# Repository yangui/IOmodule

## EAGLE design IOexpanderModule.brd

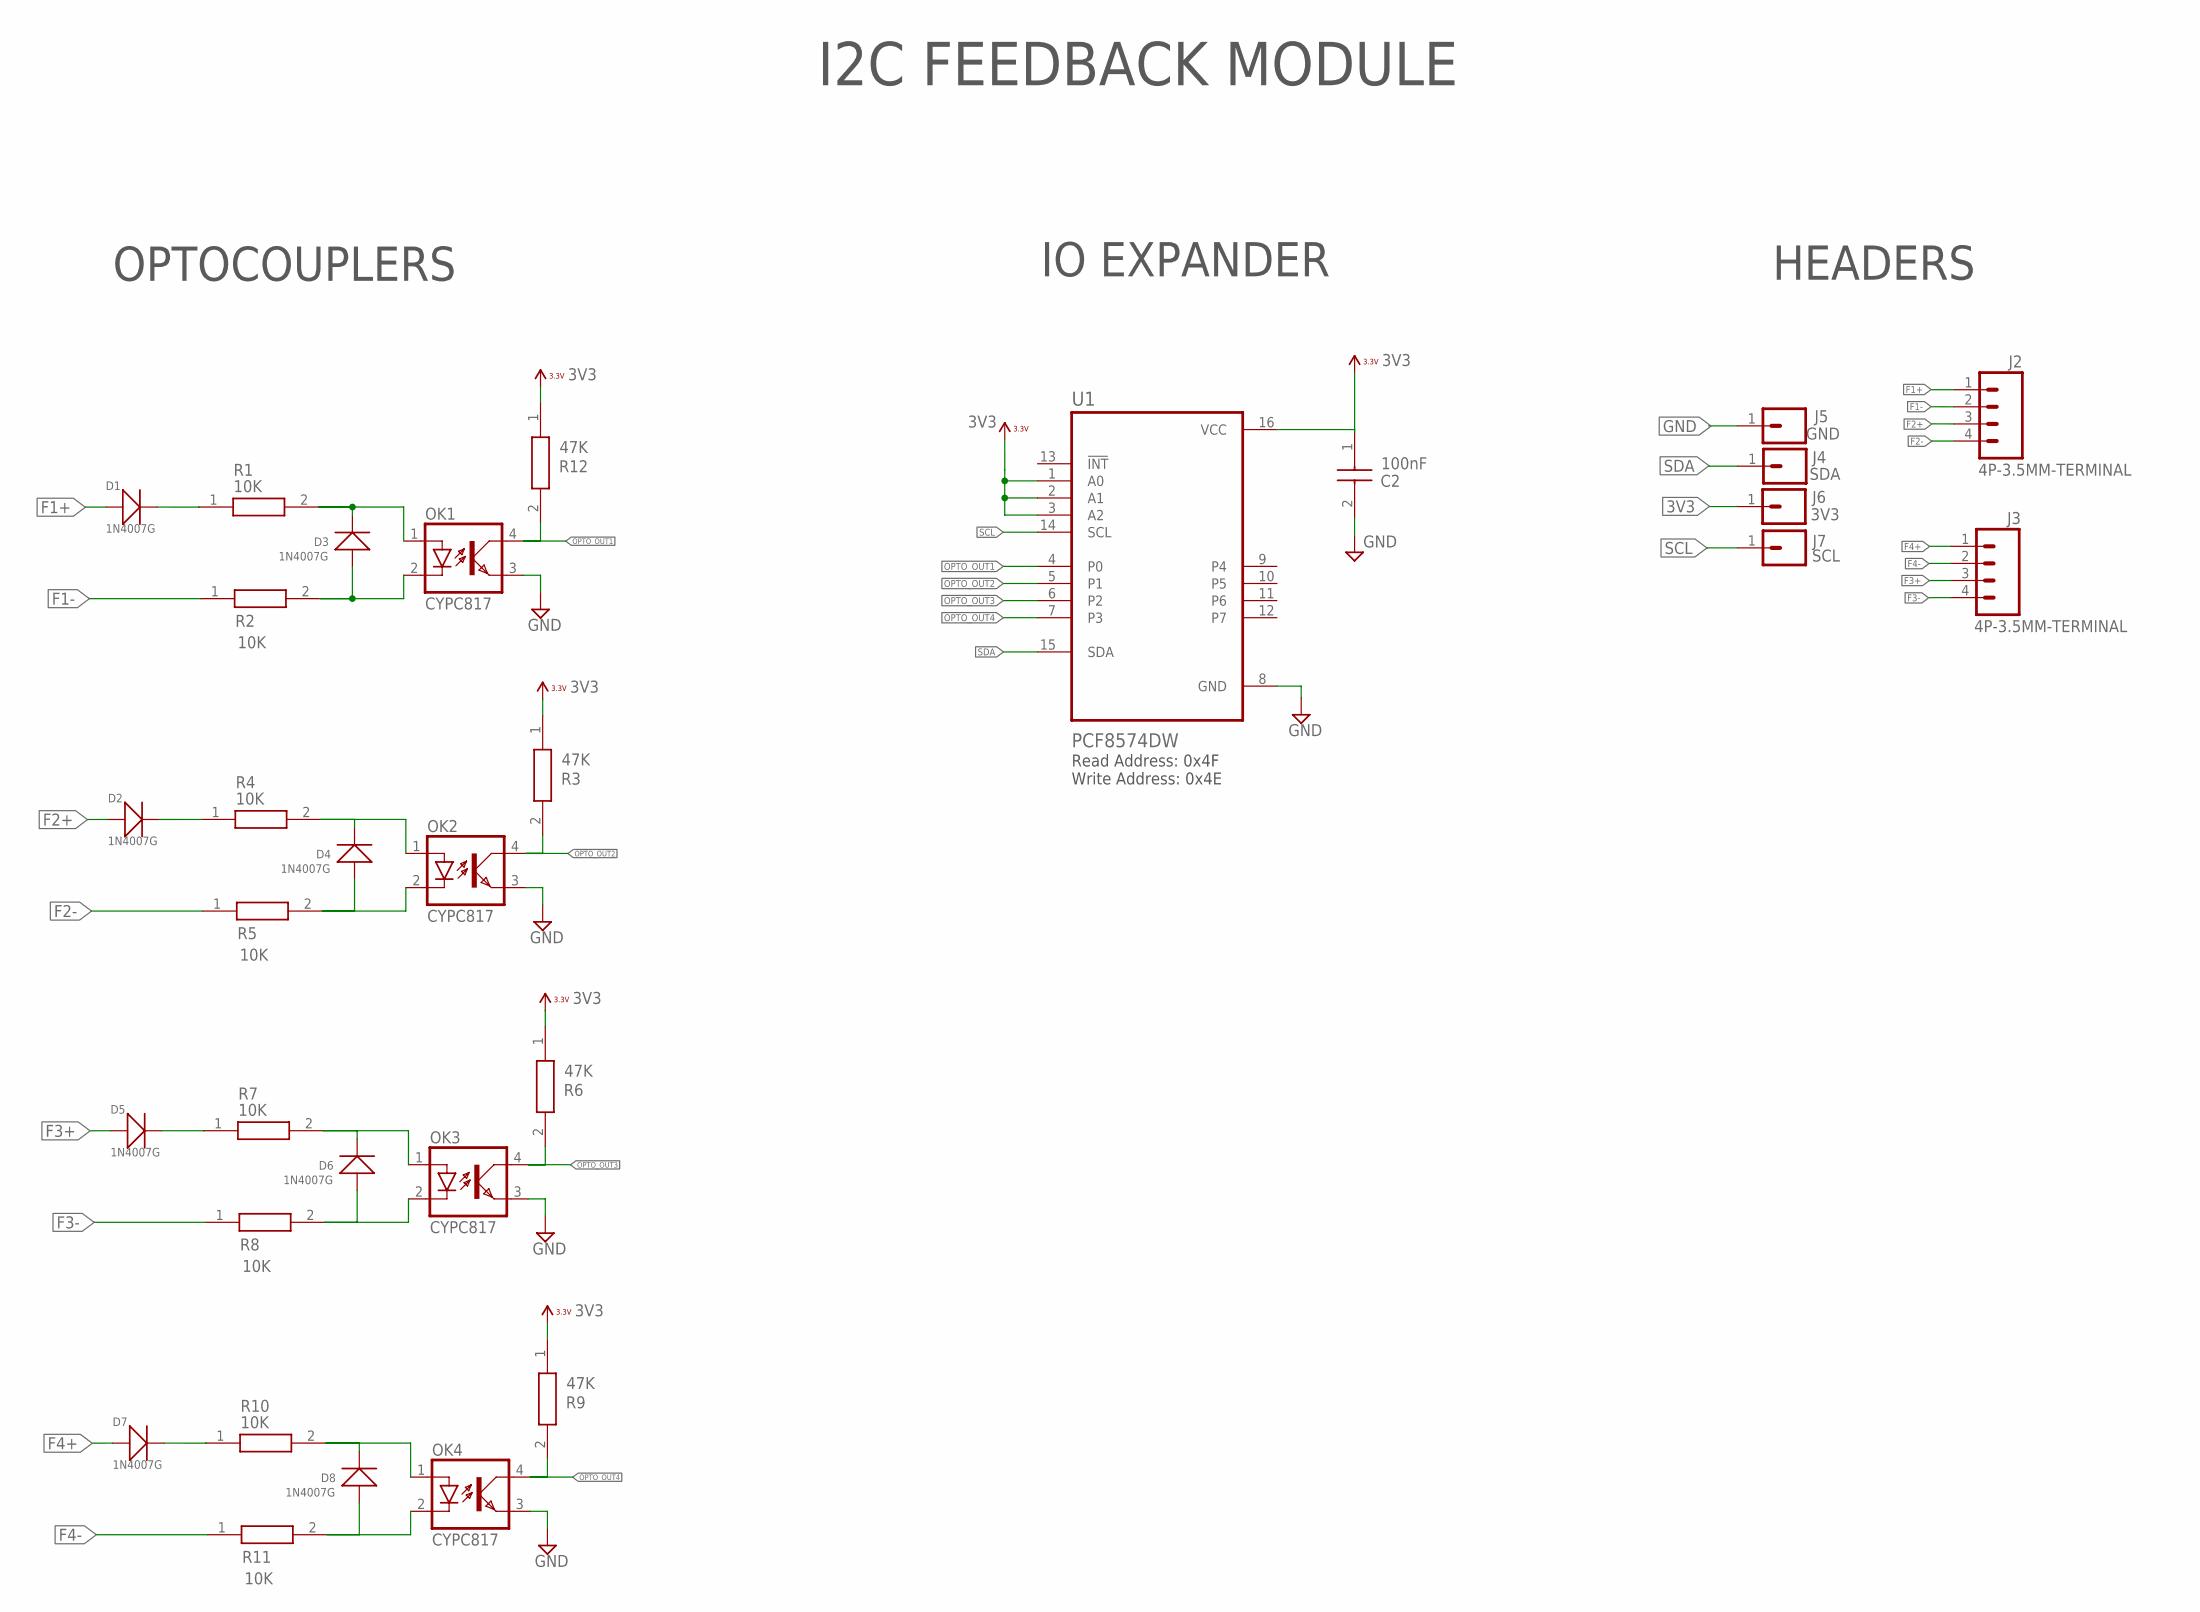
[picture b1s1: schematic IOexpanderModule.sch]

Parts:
C2: 100nF; CAPC1005X55N
D1, D2, D3, D4, D5, D6, D7, D8: 1N4007G; DO-214AC
J2: 4P-3.5MM-TERMINAL; HDRVR4W80P350_1X4_1540X690X920B; PARTNUMBER DB2EVC-3.5-4P-GN
J3: 4P-3.5MM-TERMINAL; HDRVR4W80P350_1X4_1540X690X920B
J4: SDA; 1X01; PARTNUMBER YELLOW 24AWG WIRE 150MM
J5: GND; 1X01; PARTNUMBER BLACK 24AWG WIRE 150MM
J6: 3V3; 1X01; PARTNUMBER RED 24AWG WIRE 150MM
J7: SCL; 1X01; PARTNUMBER GREEN 24AWG WIRE 150MM
OK1, OK2, OK3, OK4: CYPC817; DIL4-SMD
R1, R2, R4, R5, R7, R8, R10, R11: 10K; ERJP06D_1000V
R3, R6, R9, R12: 47K; ERJ2RKD1004X
U1: PCF8574DW; SOIC127P1030X265-16N

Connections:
3V3: C2.1, J6.1, R3.1, R6.1, R9.1, R12.1, U1.1 (A0), U1.2 (A1), U1.3 (A2), U1.16 (VCC)
F1+: D1.1 (+), J2.1
F1-: J2.2, R2.1
F2+: D2.1 (+), J2.3
F2-: J2.4, R5.1
F3+: D5.1 (+), J3.3
F3-: J3.4, R8.1
F4+: D7.1 (+), J3.1
F4-: J3.2, R11.1
GND: C2.2, J5.1, OK1.3 (EMIT), OK2.3 (EMIT), OK3.3 (EMIT), OK4.3 (EMIT), U1.8 (GND)
unnamed: D4.2 (-), OK2.1 (A), R4.2
unnamed: D3.2 (-), OK1.1 (A), R1.2
unnamed: D4.1 (+), OK2.2 (C), R5.2
unnamed: D2.2 (-), R4.1
unnamed: D1.2 (-), R1.1
unnamed: D6.2 (-), OK3.1 (A), R7.2
unnamed: D6.1 (+), OK3.2 (C), R8.2
unnamed: D5.2 (-), R7.1
unnamed: D8.2 (-), OK4.1 (A), R10.2
unnamed: D8.1 (+), OK4.2 (C), R11.2
unnamed: D7.2 (-), R10.1
unnamed: D3.1 (+), OK1.2 (C), R2.2
OPTO_OUT1: OK1.4 (COL), R12.2, U1.4 (P0)
OPTO_OUT2: OK2.4 (COL), R3.2, U1.5 (P1)
OPTO_OUT3: OK3.4 (COL), R6.2, U1.6 (P2)
OPTO_OUT4: OK4.4 (COL), R9.2, U1.7 (P3)
SCL: J7.1, U1.14 (SCL)
SDA: J4.1, U1.15 (SDA)

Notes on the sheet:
IO EXPANDER
HEADERS
OPTOCOUPLERS
Read Address: 0x4F Write Address: 0x4E
I2C FEEDBACK MODULE

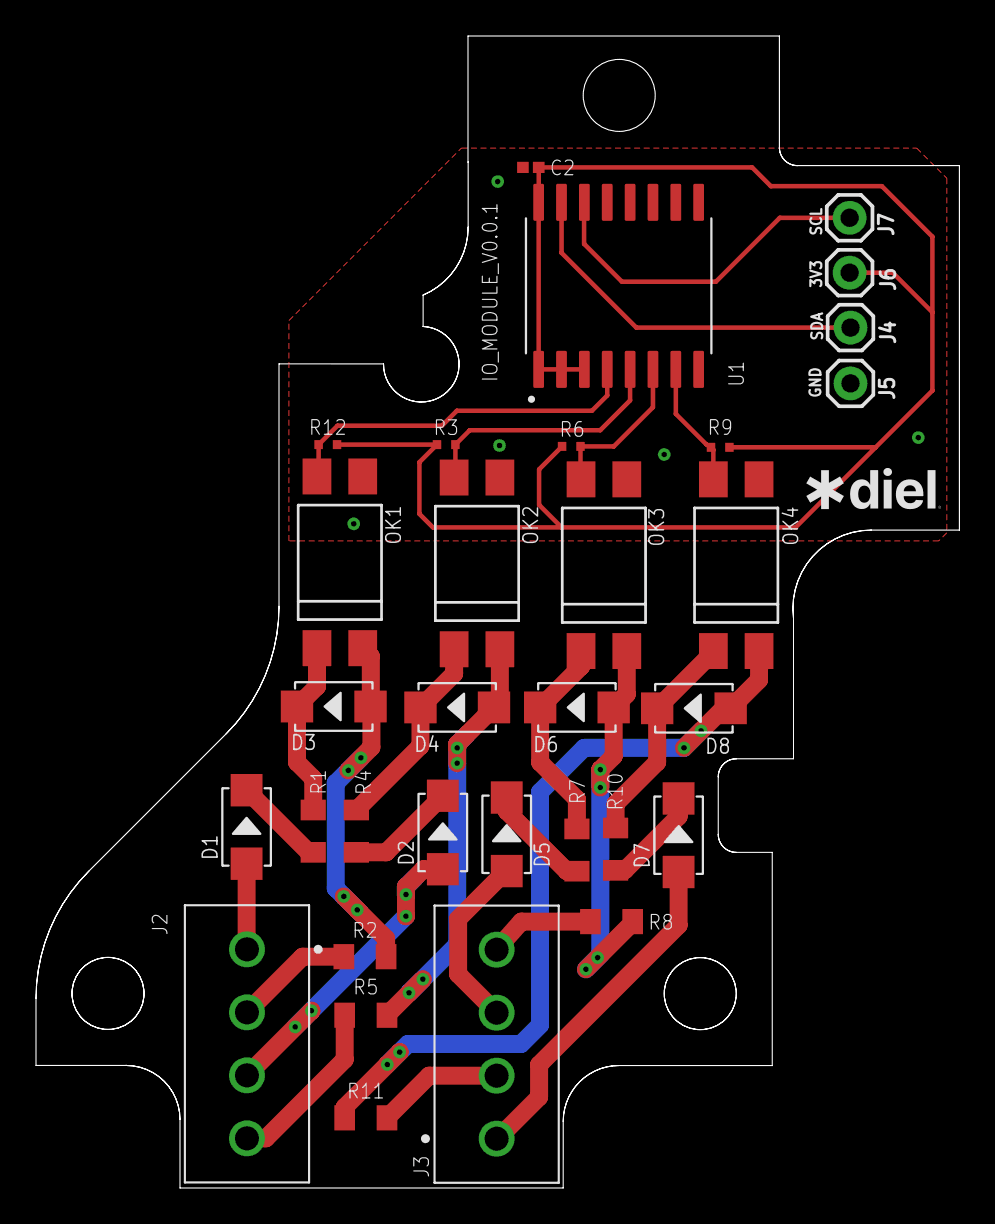
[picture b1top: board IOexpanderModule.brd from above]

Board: 2 copper layers, 51.3 x 64.0 mm, 32 parts (0 on the bottom side), 28 nets.

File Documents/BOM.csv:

"Qty";"Value";"Device";"Package";"Parts";"Description";"PARTNUMBER";"PARTNUMBER2";"PARTNUMBER3";"PARTNUMBER4";
"1";"100nF";"C0402C104K4RAC";"CAPC1005X55N";"C2";"Multilayer Ceramic Capacitors MLCC - SMD/SMT 16volts 0.1uF 10% X7R";"C0402C104K4RAC";"C0402C104K8RAC";"CC0402KRX7R8BB104";"";
"8";"10K";"ERJ-P06J103V";"ERJP06D_1000V";"R1, R2, R4, R5, R7, R8, R10, R11";"Thick Film Resistors - SMD 0805 10Kohms 0.5W 5% AEC-Q200";"ERJ-P06J103V";"SDR10EZPJ103";"ERJ-P06F1002V";"";
"8";"1N4007G";"SMD-DIODE-SCHOTTKY-40V-1A(DO-214AC)";"DO-214AC";"D1, D2, D3, D4, D5, D6, D7, D8";"304020027";"S1M-13-F";"";"";"";
"1";"3V3";"CONN_01_PAD";"1X01";"J6";"";"RED 24AWG WIRE 150MM";"";"";"";
"4";"47K";"ERJ-2RKF4702X";"ERJ2RKD1004X";"R3, R6, R9, R12";"Precision Thick Film Chip Resistor, 47Kohm, 0402, 1/10W";"ERJ-2RKF4702X";"ERJ-2GEJ473X";"RCS040247K0FKED";"";
"2";"4P-3.5MM-TERMINAL";"TERMINAL-PLUG-4P-3,5TERMINAL-3.5-4P";"HDRVR4W80P350_1X4_1540X690X920B";"J2, J3";"TERMINAL BLOCK, 3.5MM PITCH, 4 POLES, 180 DEGREES";"DB2EVC-3.5-4P-GN";"KF2EDGV-3.5-4P";"395016004";"284514-4";
"4";"CYPC817";"LTV816S";"DIL4-SMD";"OK1, OK2, OK3, OK4";"OPTO COUPLER";"CYPC817(C-TP2)";"TPC817S1C RAG";"";"";
"1";"GND";"CONN_01_PAD";"1X01";"J5";"";"BLACK 24AWG WIRE 150MM";"";"";"";
"1";"PCF8574DW";"PCF8574DW";"SOIC127P1030X265-16N";"U1";"8-bit 2.5- to 5.5-V I2C/SMBus I/O expander with interrupt";"PCF8574DWR";"";"";"";
"1";"SCL";"CONN_01_PAD";"1X01";"J7";"";"GREEN 24AWG WIRE 150MM";"";"";"";
"1";"SDA";"CONN_01_PAD";"1X01";"J4";"";"YELLOW 24AWG WIRE 150MM";"";"";"";

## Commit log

2023-05-18 project init
2023-05-19 added: logo, board name, fixed: resistors silkscreen names,
2023-05-19 CAM and CAD files added

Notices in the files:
parts and their libraries:
PatternAgents-Beautify: License : http://creativecommons.org/licenses/by-sa/3.0
(Creative Commons 3.0)
